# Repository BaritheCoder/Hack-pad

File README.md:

# Hack-pad

My Hack-pad project repository.

()

---

## Design Overview

| Case | PCB | Schematic |
|------|-----|-----------|
|  |  |  |

---

## Challenges

This was my first time using a PCB design program, but I really enjoyed the process and I’m looking forward to my next project that requires custom PCBs.

Although I have used CAD programs before, this project helped me learn many new things about both **PCB design** and **3D modeling**.

---

## Specifications

### Bill of Materials (BOM)

- **6×** Cherry MX switches  
- **3×** SK6812 MINI LEDs  
- **1×** XIAO RP2040  
- **1×** Rotary Encoder (Alps EC11E, vertical, with switch)  
- **6×** Blank DSA keycaps  
- **4×** M3×16 bolts  
- **4×** M3 heat-set inserts  

### Other Files & Tools
- KMK firmware  
- `Top Case.stl`  
- `Bottom Case.stl`  

---

## V2 Changes
- Changed LED position  
- Fixed schematic routing issue

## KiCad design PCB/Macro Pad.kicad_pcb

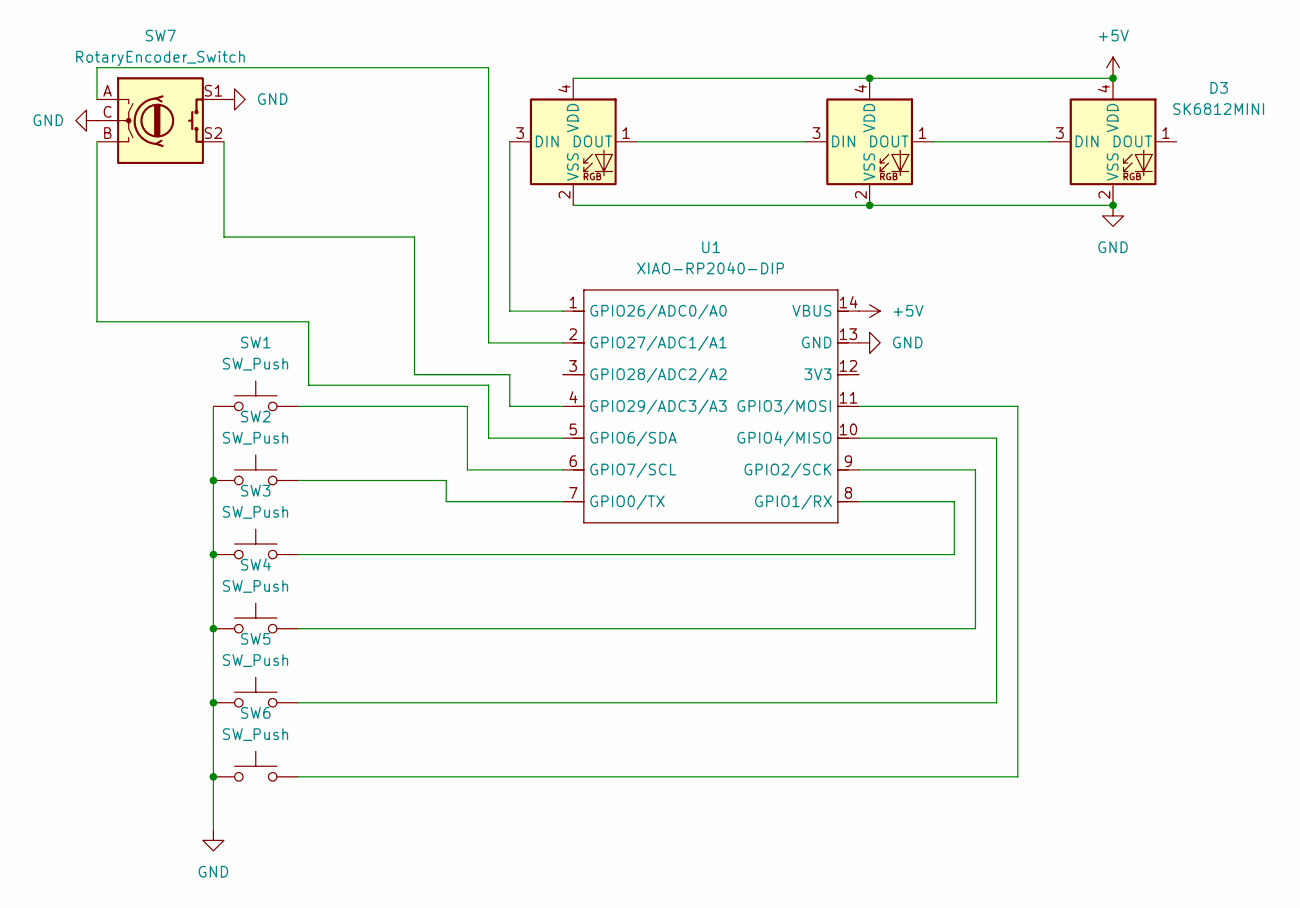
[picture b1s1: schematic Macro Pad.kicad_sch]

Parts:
D1, D2, D3: SK6812MINI; LED_SK6812MINI_PLCC4_3.5x3.5mm_P1.75mm
SW1, SW2, SW3, SW4, SW5, SW6: SW_Push; SW_Cherry_MX_1.00u_PCB
SW7: RotaryEncoder_Switch; RotaryEncoder_Alps_EC11E-Switch_Vertical_H20mm
U1: XIAO-RP2040-DIP

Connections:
+5V: D1.4 (VDD), D2.4 (VDD), D3.4 (VDD), U1.14 (VBUS)
GND: D1.2 (VSS), D2.2 (VSS), D3.2 (VSS), SW1.1, SW2.1, SW3.1, SW4.1, SW5.1, SW6.1, SW7.C, SW7.S1, U1.13 (GND)
unnamed: D1.3 (DIN), U1.1 (GPIO26/ADC0/A0)
unnamed: D1.1 (DOUT), D2.3 (DIN)
unnamed: D2.1 (DOUT), D3.3 (DIN)
unnamed: SW2.2, U1.7 (GPIO0/TX)
unnamed: SW3.2, U1.8 (GPIO1/RX)
unnamed: SW4.2, U1.9 (GPIO2/SCK)
unnamed: SW6.2, U1.11 (GPIO3/MOSI)
unnamed: SW5.2, U1.10 (GPIO4/MISO)
unnamed: SW7.B, U1.5 (GPIO6/SDA)
unnamed: SW1.2, U1.6 (GPIO7/SCL)
unnamed: SW7.A, U1.2 (GPIO27/ADC1/A1)
unnamed: SW7.S2, U1.4 (GPIO29/ADC3/A3)

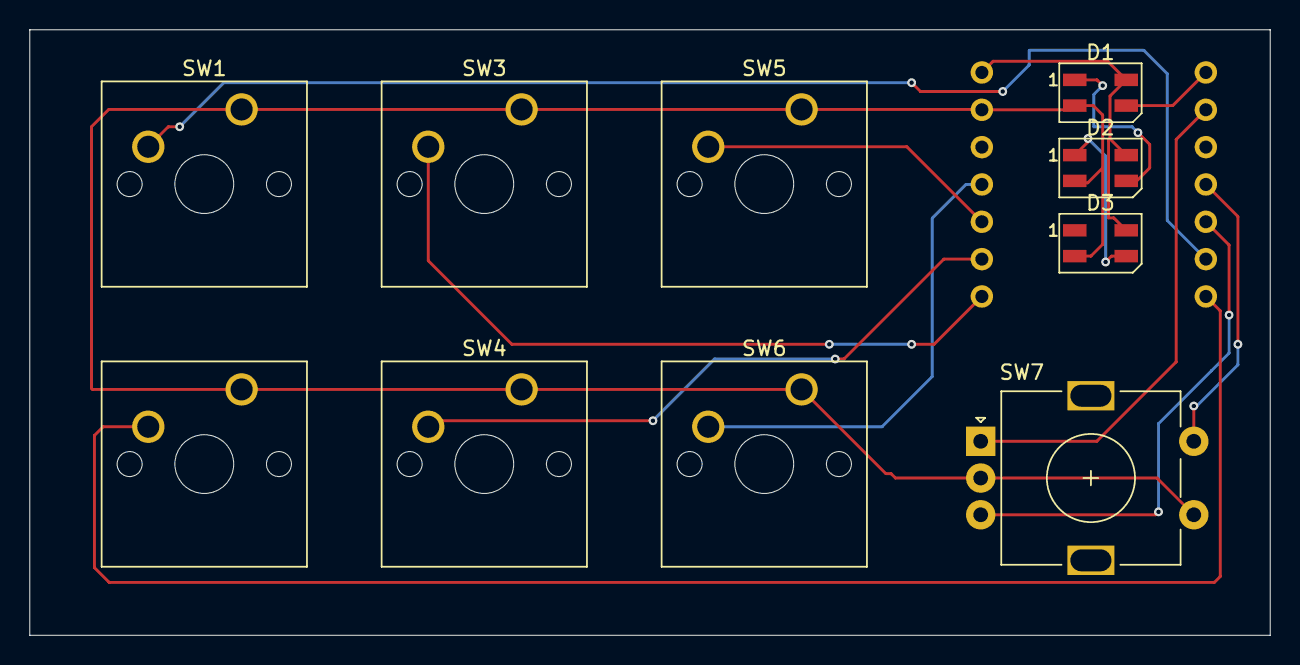
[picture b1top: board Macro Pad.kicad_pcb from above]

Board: 2 copper layers, 84.4 x 41.2 mm, 11 parts (1 on the bottom side), 14 nets.

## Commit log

2026-01-23 Update files
2026-01-24 Images upload
2026-01-24 Add image to README.md
2026-01-24 Add second screenshot to README
2026-01-24 Update README with project challenges and specifications
    Added project challenges and specifications including BOM.
2026-01-24 Fix image link and typos in README
    Updated image link in README and corrected typos.
2026-01-24 Update image and fix typos in README
    Replaced an image in the README and corrected typos in the text.
2026-01-24 Update README with new image and typo corrections
    Added an additional image to the README and corrected typos in the challenges section.
2026-01-24 Revise README with project details and specifications
    Updated project description, added design overview and challenges sections, and improved specifications formatting.
2026-01-24 Update PCB image link in README
2026-01-24 Update schematic image link in README
    Fixed image link for schematic in README.
2026-01-24 Fix image link for schematic in README
2026-01-24 Correct image link in README.md
    Fix image link formatting in the README table.
2026-01-24 Update README with image links and V2 changes
    Fixed image link formatting and added V2 changes section.
2026-01-24 Fix V2 changes header and update details
    Correct formatting and update V2 changes section.
2026-01-24 Fix typos in V2 changes section of README
2026-02-19 Add files
2026-02-19 Update V2 changes section in README
2026-02-19 Correct image link syntax in README
    Fix image link formatting in README.md
2026-02-19 Fix image links and update V2 changes section
    Updated image links and fixed formatting issues in the README.
2026-02-19 Fix image link formatting in README.md
2026-02-19 Fix image syntax in README.md
